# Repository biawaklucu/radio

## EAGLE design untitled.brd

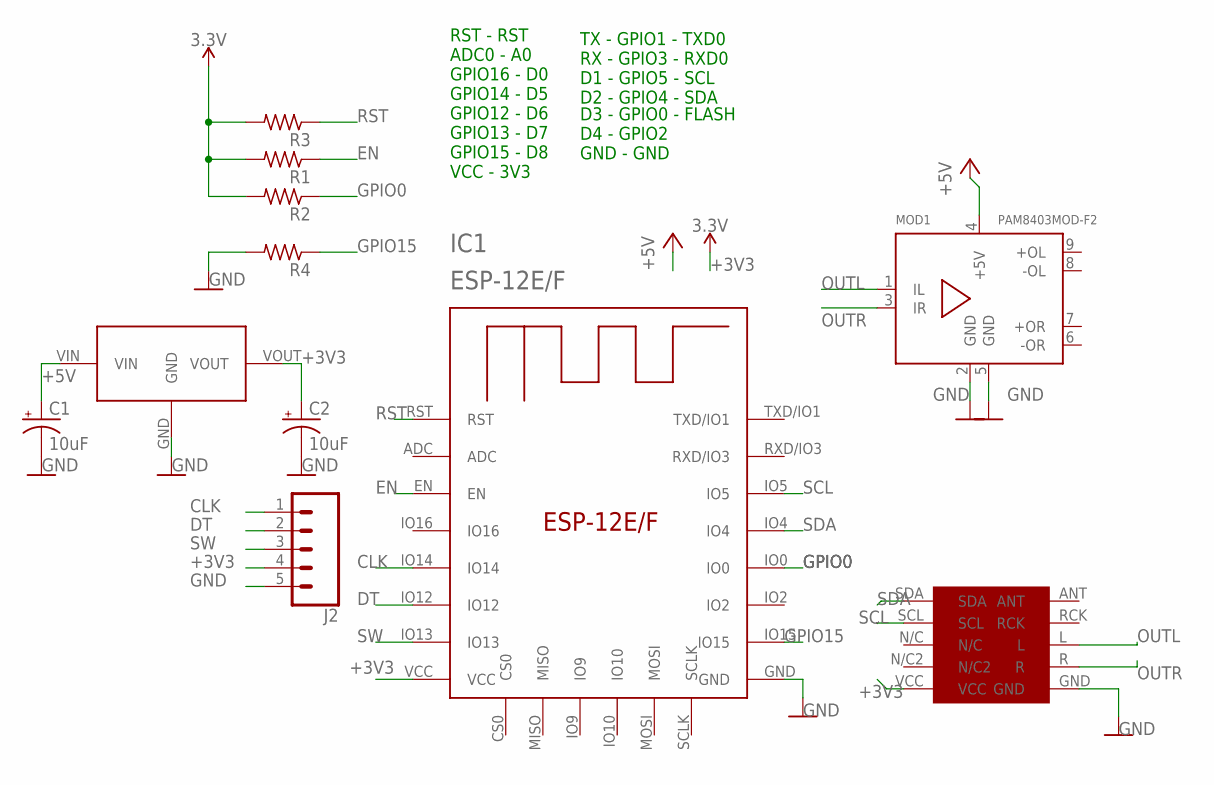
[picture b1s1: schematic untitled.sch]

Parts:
C1, C2: 10uF; EIA3216
IC1: ESP-12E/F; ESP-12E
J2: CONN_05PTH_LONGPADS; 1X05_LONGPADS
MOD1: PAM8403MOD-F2; PAM8403MOD2
R1, R2, R3, R4: R-US_R0805; R0805
U$1: RDA
U$2: HT7333; SOT89

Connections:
3.3V: R1.2, R2.2, R3.2
+3V3: C2.A (+), IC1.VCC, J2.4, U$1.VCC, U$2.VOUT
+5V: C1.A (+), MOD1.4 (+5V), U$2.VIN
CLK: IC1.IO14, J2.1
DT: IC1.IO12, J2.2
EN: IC1.EN, R1.1
GND: C1.C (-), C2.C (-), IC1.GND, J2.5, MOD1.2 (GND), MOD1.5 (GND), R4.2, U$1.GND, U$2.GND
GPIO0: IC1.IO0, R2.1
GPIO15: IC1.IO15, R4.1
OUTL: MOD1.1 (IL), U$1.L
OUTR: MOD1.3 (IR), U$1.R
RST: IC1.RST, R3.1
SCL: IC1.IO5, U$1.SCL
SDA: IC1.IO4, U$1.SDA
SW: IC1.IO13, J2.3

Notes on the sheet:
RST - RST ADC0 - A0 GPIO16 - D0 GPIO14 - D5 GPIO12 - D6 GPIO13 - D7 GPIO15 - D8 VCC - 3V3
TX - GPIO1 - TXD0 RX - GPIO3 - RXD0 D1 - GPIO5 - SCL D2 - GPIO4 - SDA
D3 - GPIO0 - FLASH D4 - GPIO2 GND - GND

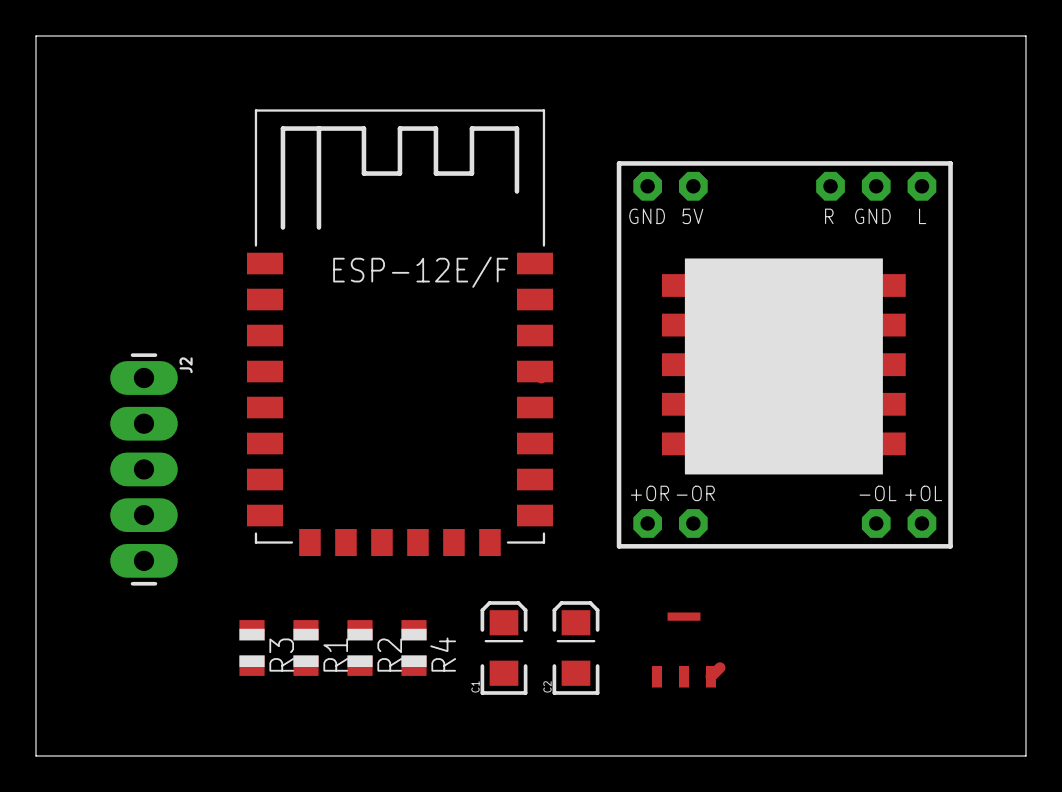
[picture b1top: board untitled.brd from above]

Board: 2 copper layers, 55.0 x 40.0 mm, 11 parts (0 on the bottom side), 15 nets.

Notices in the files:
parts and their libraries:
SparkFun-Retired: Licensing: Creative Commons ShareAlike 4.0 International - https://creativecommons.org/licenses/by-sa/4.0
